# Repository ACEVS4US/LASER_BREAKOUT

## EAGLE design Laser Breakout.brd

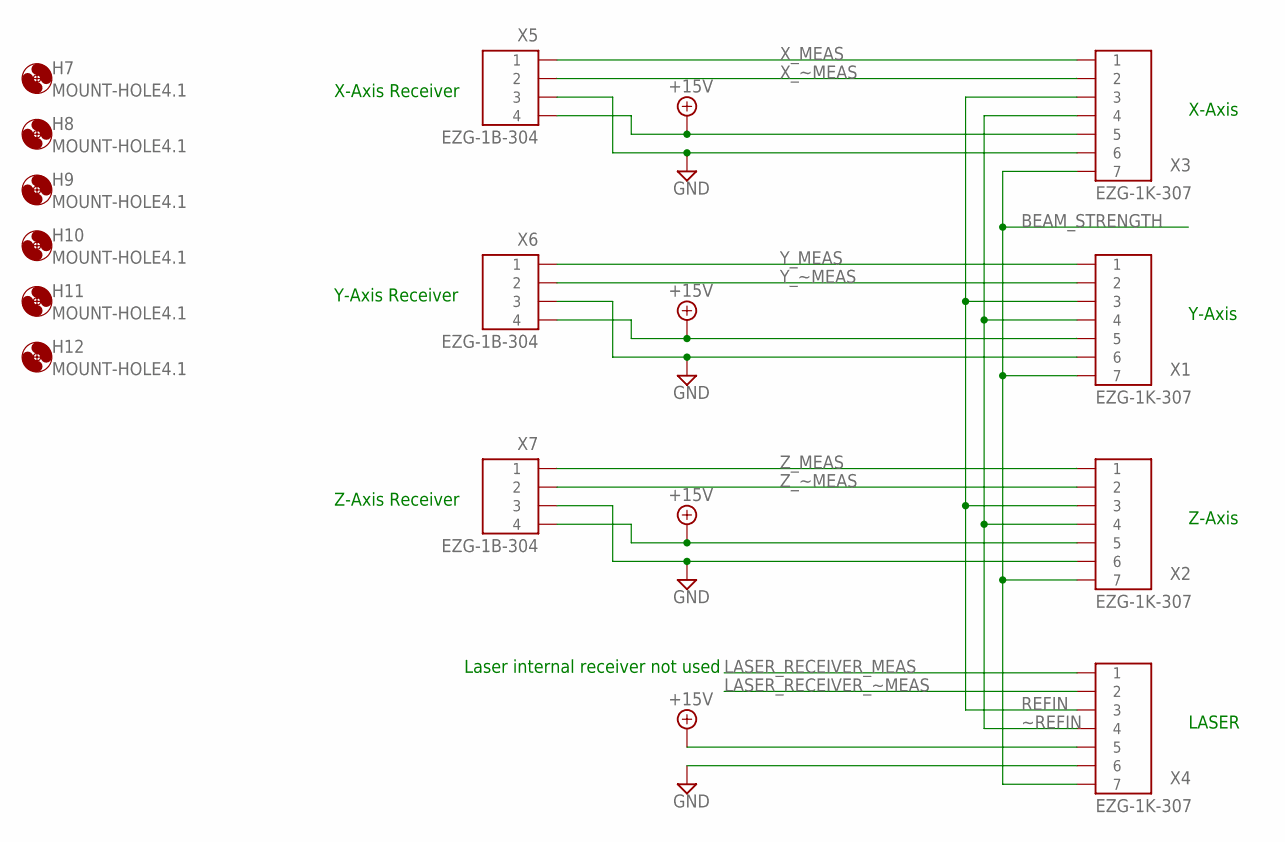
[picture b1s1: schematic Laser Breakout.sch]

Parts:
H7, H8, H9, H10, H11, H12: MOUNT-HOLE4.1; 4,1
X1, X2, X3, X4: EZG-1K-307; EZG-1B-1K-307
X5, X6, X7: EZG-1B-304; EZG-1B-1K-304

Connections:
+15V: X1.5, X2.5, X3.5, X4.5, X5.4, X6.4, X7.4
BEAM_STRENGTH: X1.7, X2.7, X3.7, X4.7
GND: X1.6, X2.6, X3.6, X4.6, X5.3, X6.3, X7.3
LASER_RECEIVER_MEAS: X4.1
LASER_RECEIVER_~MEAS: X4.2
REFIN: X1.3, X2.3, X3.3, X4.3
X_MEAS: X3.1, X5.1
X_~MEAS: X3.2, X5.2
Y_MEAS: X1.1, X6.1
Y_~MEAS: X1.2, X6.2
Z_MEAS: X2.1, X7.1
Z_~MEAS: X2.2, X7.2
~REFIN: X1.4, X2.4, X3.4, X4.4

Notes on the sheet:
X-Axis
Y-Axis
Z-Axis
LASER
X-Axis Receiver
Y-Axis Receiver
Z-Axis Receiver
Laser internal receiver not used

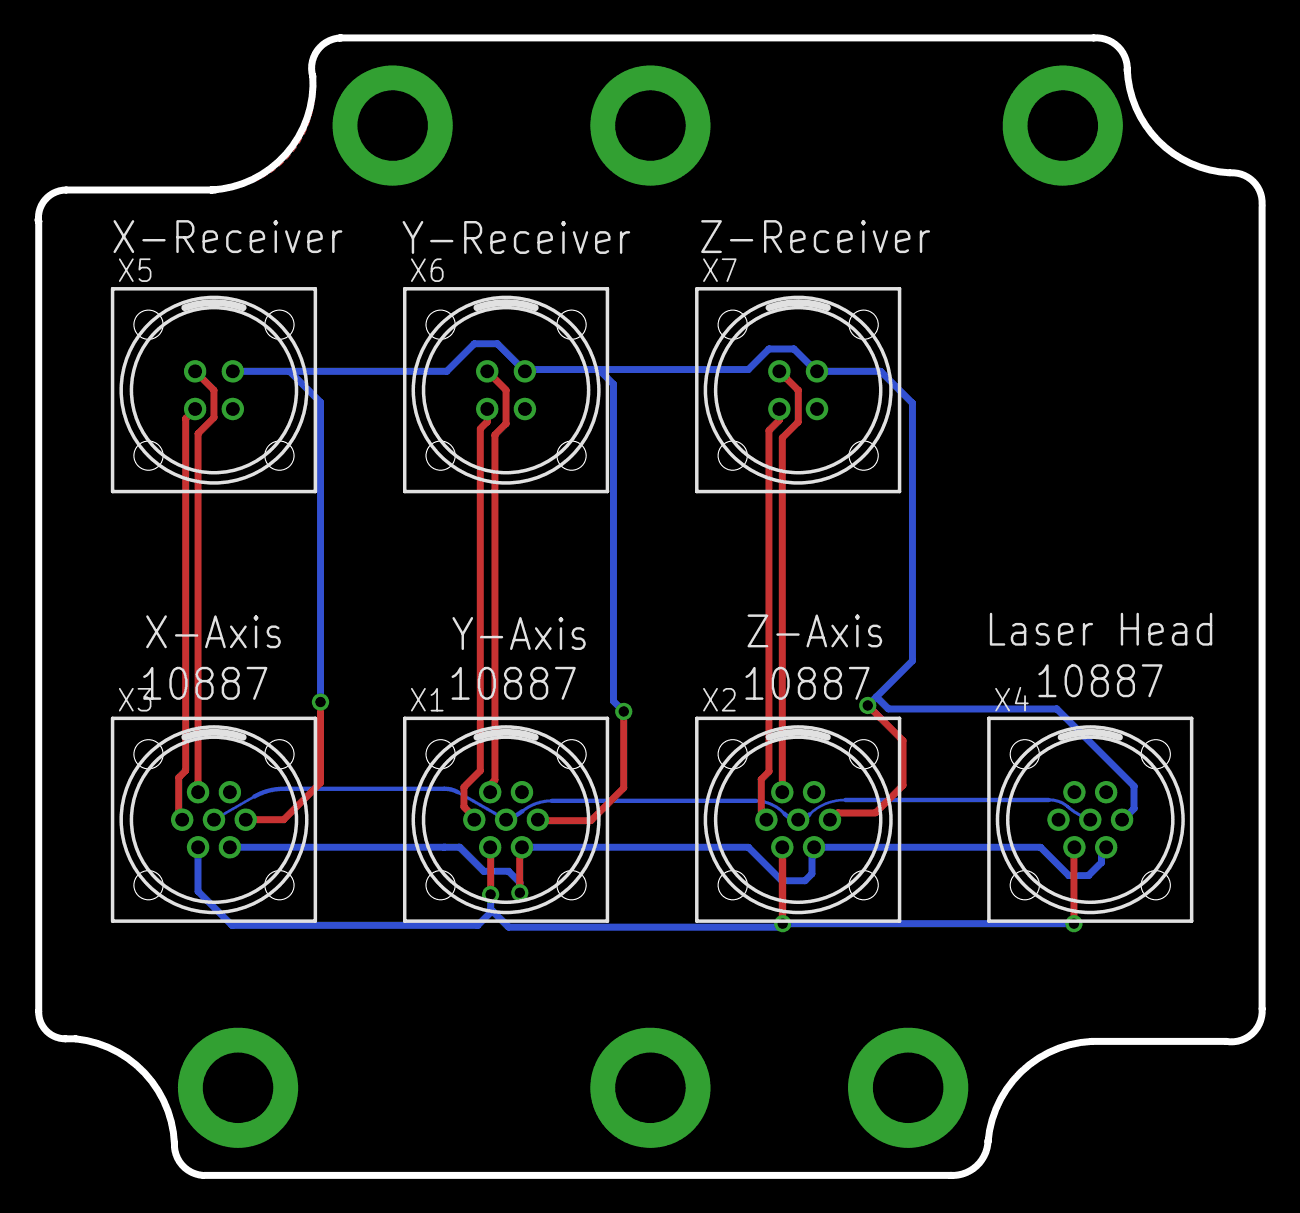
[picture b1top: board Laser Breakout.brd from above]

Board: 2 copper layers, 71.3 x 66.2 mm, 13 parts (0 on the bottom side), 11 nets.
